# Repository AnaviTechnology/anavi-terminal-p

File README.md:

# ANAVI Terminal P

ANAVI Terminal P is a simple prototyping board for Raspberry Pi Pico. Based on a Raspberry Pi Pico footprint for KiCad by Nicolò Carandini:
https://github.com/ncarandini/KiCad-RP-Pico

# License

The project is released under the [Creative Commons Attribution-ShareAlike 4.0 International (CC BY-SA 4.0)](https://creativecommons.org/licenses/by-sa/4.0/).

Note: This is a human-readable summary of (and not a substitute for) the [license](https://creativecommons.org/licenses/by-sa/4.0/legalcode).

You are free to:

Share — copy and redistribute the material in any medium or format Adapt — remix, transform, and build upon the material for any purpose, even commercially. The licensor cannot revoke these freedoms as long as you follow the license terms. Under the following terms:

Attribution — You must give appropriate credit, provide a link to the license, and indicate if changes were made. You may do so in any reasonable manner, but not in any way that suggests the licensor endorses you or your use. ShareAlike — If you remix, transform, or build upon the material, you must distribute your contributions under the same license as the original. No additional restrictions — You may not apply legal terms or technological measures that legally restrict others from doing anything the license permits. Notices:

You do not have to comply with the license for elements of the material in the public domain or where your use is permitted by an applicable exception or limitation. No warranties are given. The license may not give you all of the permissions necessary for your intended use. For example, other rights such as publicity, privacy, or moral rights may limit how you use the material.

You will have to provide a link to the original creator of the project http://www.anavi.technology on any documentation or website.

Credit can be attributed through a link to the creator website: http://www.anavi.technology

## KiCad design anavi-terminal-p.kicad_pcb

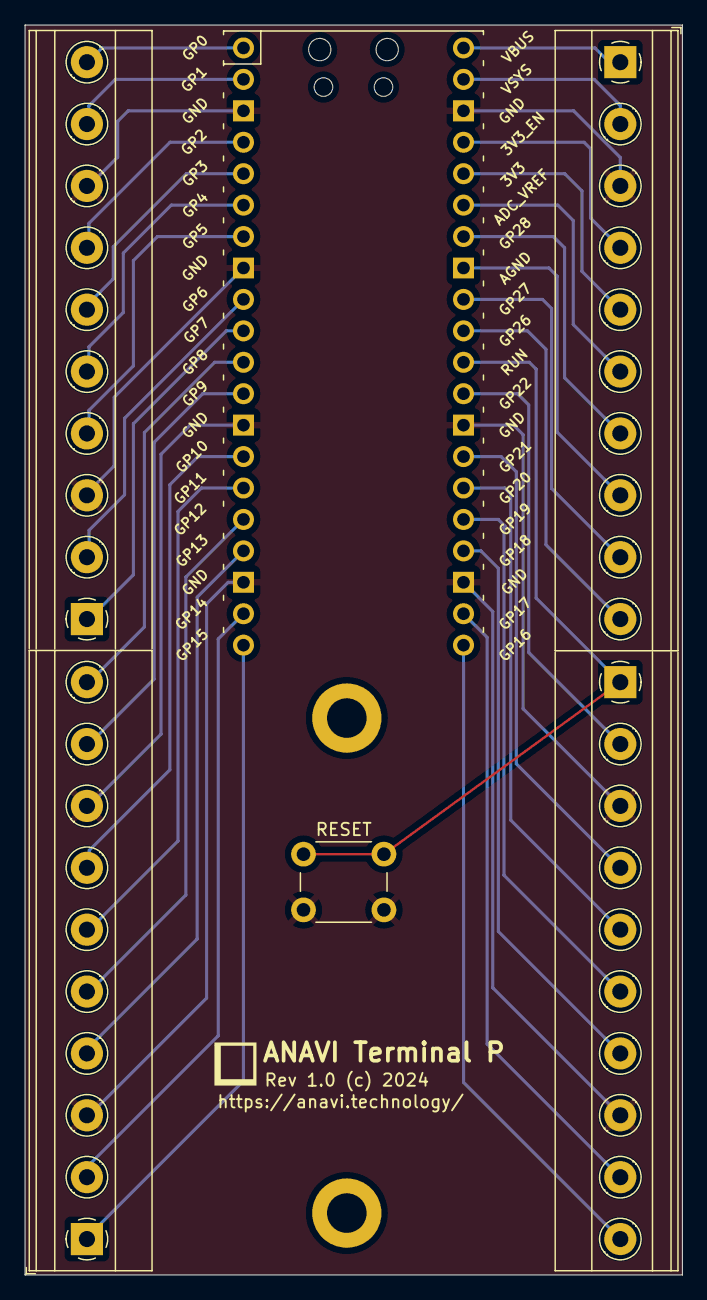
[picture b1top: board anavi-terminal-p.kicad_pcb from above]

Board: 2 copper layers, 53.1 x 101.0 mm, 6 parts (0 on the bottom side), 34 nets.

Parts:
J1, J2, J3, J4: Screw_Terminal_01x10; TerminalBlock_Phoenix_MKDS-1,5-10_1x10_P5.00mm_Horizontal
RESET: SW_DIP_x01; SW_PUSH_6mm_H4.3mm
U1: Pico; RPi_Pico_SMD_TH

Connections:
GND: J1.3, J1.8, J2.3, J2.8, J3.3, J4.3, J4.8, RESET.1, U1.3 (GND), U1.8 (GND), U1.13 (GND), U1.18 (GND), U1.23 (GND), U1.28 (GND), U1.38 (GND)
unnamed: J1.1, U1.10 (GPIO7)
unnamed: J1.2, U1.9 (GPIO6)
unnamed: J1.4, U1.7 (GPIO5)
unnamed: J1.5, U1.6 (GPIO4)
unnamed: J1.6, U1.5 (GPIO3)
unnamed: J1.7, U1.4 (GPIO2)
unnamed: J1.9, U1.2 (GPIO1)
unnamed: J1.10, U1.1 (GPIO0)
unnamed: J2.1, RESET.2, U1.30 (RUN)
unnamed: J2.2, U1.29 (GPIO22)
unnamed: J2.4, U1.27 (GPIO21)
unnamed: J2.5, U1.26 (GPIO20)
unnamed: J2.6, U1.25 (GPIO19)
unnamed: J2.7, U1.24 (GPIO18)
unnamed: J2.9, U1.22 (GPIO17)
unnamed: J2.10, U1.21 (GPIO16)
unnamed: J3.1, U1.40 (VBUS)
unnamed: J3.2, U1.39 (VSYS)
unnamed: J3.4, U1.37 (3V3_EN)
unnamed: J3.5, U1.36 (3V3)
unnamed: J3.6, U1.35 (ADC_VREF)
unnamed: J3.7, U1.34 (GPIO28_ADC2)
unnamed: J3.8, U1.33 (AGND)
unnamed: J3.9, U1.32 (GPIO27_ADC1)
unnamed: J3.10, U1.31 (GPIO26_ADC0)
unnamed: J4.1, U1.20 (GPIO15)
unnamed: J4.2, U1.19 (GPIO14)
unnamed: J4.4, U1.17 (GPIO13)
unnamed: J4.5, U1.16 (GPIO12)
unnamed: J4.6, U1.15 (GPIO11)
unnamed: J4.7, U1.14 (GPIO10)
unnamed: J4.9, U1.12 (GPIO9)
unnamed: J4.10, U1.11 (GPIO8)

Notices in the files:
anavi-terminal-p.kicad_pcb:
Rev 1.0 (c) 2024
